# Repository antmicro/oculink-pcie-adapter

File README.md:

# OCuLink to PCIe adapter
Copyright (c) 2025 [Antmicro](https://www.antmicro.com)

## Overview

This project includes PCB design files for an adapter card which break-routes a regular OCuLink x4 connector into x16 PCIe edge card slot.
This board was designed for use with Antmicro [Jetson Orin Baseboard OCuLink Expansion](https://github.com/antmicro/job-oculink-expansion).
Please inspect the schematics and verify the connection diagrams if you plan to use that board with any other OCuLink-compliant accessories.
The PCB design files were prepared in KiCad 9.x 

## Key features

- Supports 4x PCIe link via an OCuLink connector over an x16 card edge connector
- PCIe cards can be powered via USB-C Power Delivery, EPS-12V or Molex Nano-Fit connector
- Optional on-board PCIe clock generator for SRSI and SRNS clocking configurations
- Mechanical outline optimized for  dual slot PCIe cards

## Project structure

The main directory contains KiCad PCB project files and README. 
The remaining files are stored in the following directories:

-   `img` - contains graphics for this README

## Licensing

This project is published under the [Apache-2.0](LICENSE) license.

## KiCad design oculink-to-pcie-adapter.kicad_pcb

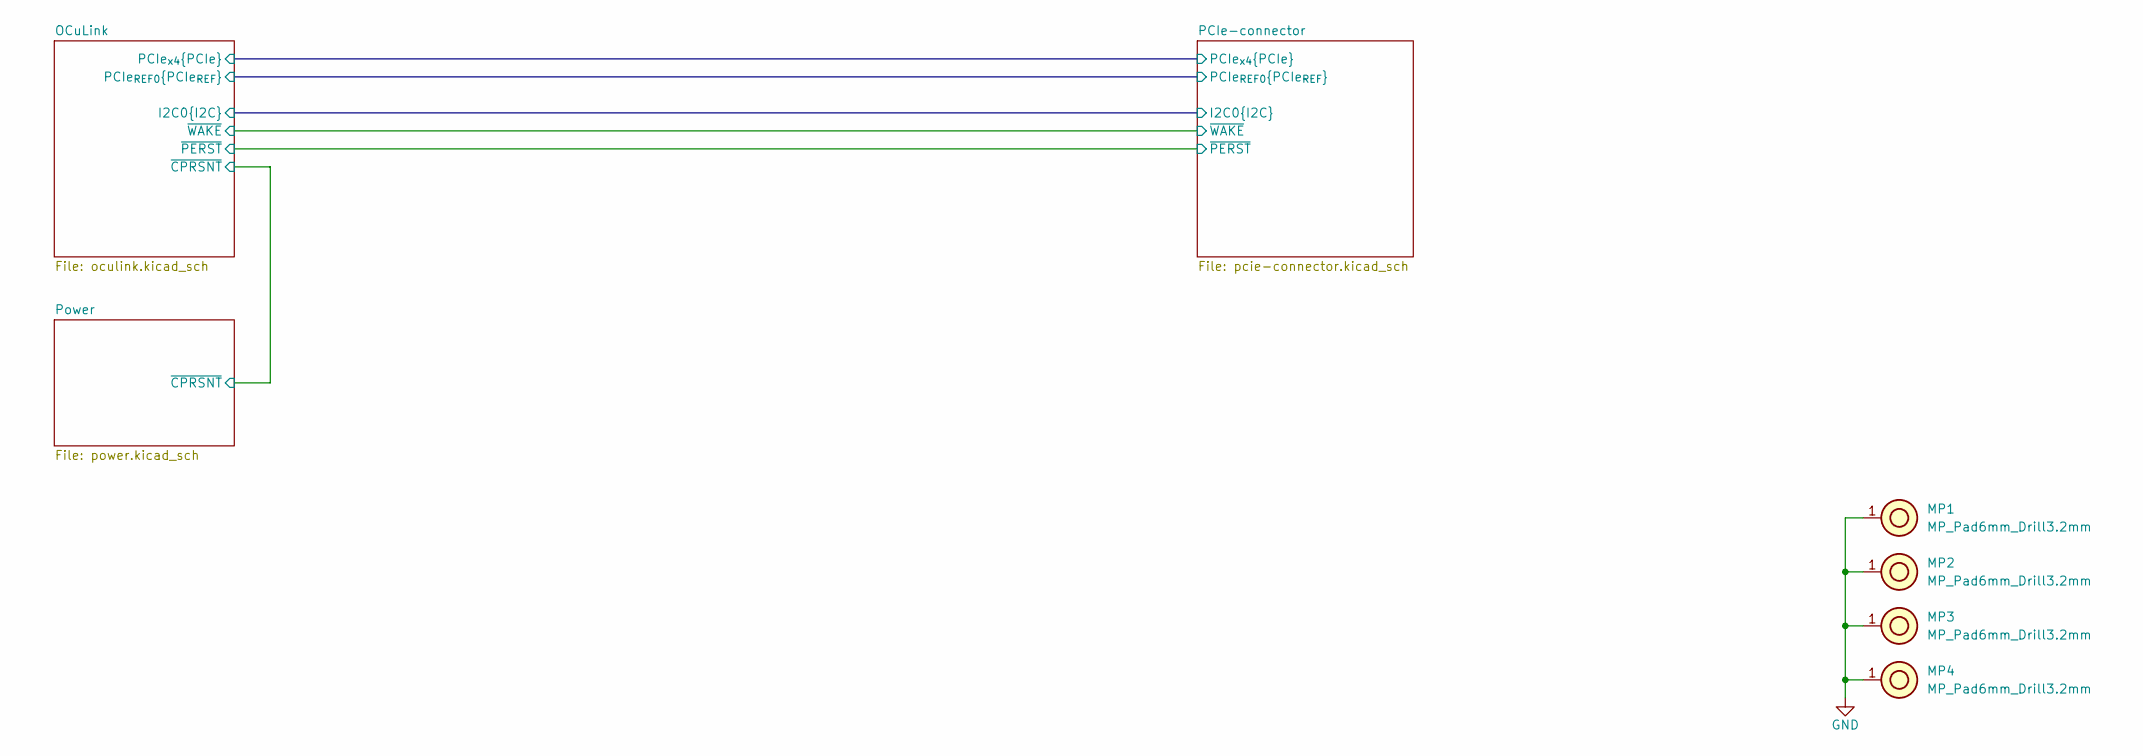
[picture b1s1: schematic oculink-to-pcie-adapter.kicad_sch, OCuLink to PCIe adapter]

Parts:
MP1, MP2, MP3, MP4: MP_Pad6mm_Drill3.2mm

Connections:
GND: MP1.1, MP2.1, MP3.1, MP4.1; also elsewhere on the board

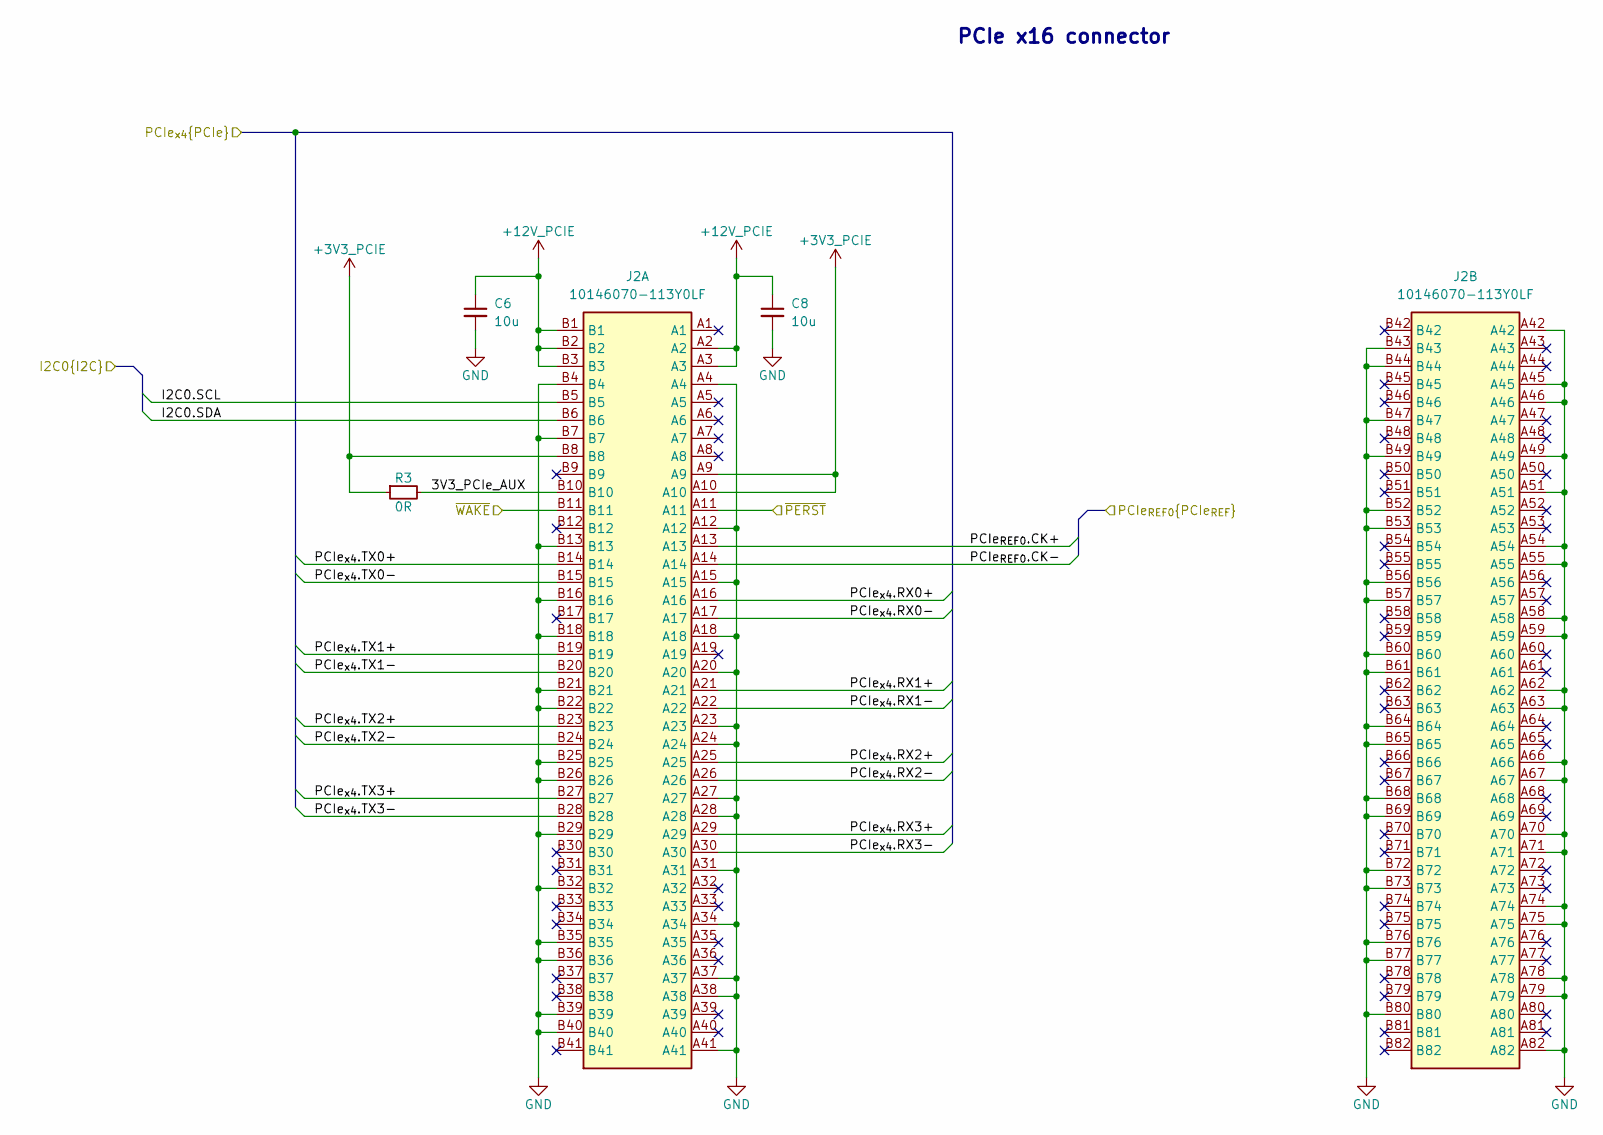
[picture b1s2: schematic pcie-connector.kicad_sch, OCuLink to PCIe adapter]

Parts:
C6, C8: C_10u_0805_35V; C_0805_2012Metric; Voltage 35V; MPN GRM21BR6YA106KE43L
J2: PCIe_x16_10146070-113Y0LF-vertical; AMPHENOL_10146070-113Y0LF; PARTREV E
R3: R_0R_0402; R_0402_1005Metric; MPN ERJ2GE0R00X

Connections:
+3V3_PCIE: J2.A9, J2.A10, J2.B8, R3.1; also elsewhere on the board
+12V_PCIE: C6.1, C8.1, J2.A2, J2.A3, J2.B1, J2.B2, J2.B3; also elsewhere on the board
/OCuLink/I2C0.SCL: J2.B5; also elsewhere on the board
/OCuLink/I2C0.SDA: J2.B6; also elsewhere on the board
/OCuLink/PCIe_{REF0}.CK+: J2.A13; also elsewhere on the board
/OCuLink/PCIe_{REF0}.CK-: J2.A14; also elsewhere on the board
/OCuLink/PCIe_{x4}.RX0+: J2.A16; also elsewhere on the board
/OCuLink/PCIe_{x4}.RX0-: J2.A17; also elsewhere on the board
/OCuLink/PCIe_{x4}.RX1+: J2.A21; also elsewhere on the board
/OCuLink/PCIe_{x4}.RX1-: J2.A22; also elsewhere on the board
/OCuLink/PCIe_{x4}.RX2+: J2.A25; also elsewhere on the board
/OCuLink/PCIe_{x4}.RX2-: J2.A26; also elsewhere on the board
/OCuLink/PCIe_{x4}.RX3+: J2.A29; also elsewhere on the board
/OCuLink/PCIe_{x4}.RX3-: J2.A30; also elsewhere on the board
/OCuLink/PCIe_{x4}.TX0+: J2.B14; also elsewhere on the board
/OCuLink/PCIe_{x4}.TX0-: J2.B15; also elsewhere on the board
/OCuLink/PCIe_{x4}.TX1+: J2.B19; also elsewhere on the board
/OCuLink/PCIe_{x4}.TX1-: J2.B20; also elsewhere on the board
/OCuLink/PCIe_{x4}.TX2+: J2.B23; also elsewhere on the board
/OCuLink/PCIe_{x4}.TX2-: J2.B24; also elsewhere on the board
/OCuLink/PCIe_{x4}.TX3+: J2.B27; also elsewhere on the board
/OCuLink/PCIe_{x4}.TX3-: J2.B28; also elsewhere on the board
/OCuLink/~PERST: J2.A11; also elsewhere on the board
/OCuLink/~WAKE: J2.B11; also elsewhere on the board
/PCIe-connector/3V3_PCIe_AUX: J2.B10, R3.2
GND: C6.2, C8.2, J2.A4, J2.A12, J2.A15, J2.A18, J2.A20, J2.A23, J2.A24, J2.A27, J2.A28, J2.A31, J2.A34, J2.A37, J2.A38, J2.A41, J2.A42, J2.A45, J2.A46, J2.A49, J2.A51, J2.A54, J2.A55, J2.A58, J2.A59, J2.A62, J2.A63, J2.A66, J2.A67, J2.A70, J2.A71, J2.A74, J2.A75, J2.A78, J2.A79, J2.A82, J2.B4, J2.B7, J2.B13, J2.B16, J2.B18, J2.B21, J2.B22, J2.B25, J2.B26, J2.B29, J2.B32, J2.B35, J2.B36, J2.B39, J2.B40, J2.B43, J2.B44, J2.B47, J2.B49, J2.B52, J2.B53, J2.B56, J2.B57, J2.B60, J2.B61, J2.B64, J2.B65, J2.B68, J2.B69, J2.B72, J2.B73, J2.B76, J2.B77, J2.B80; also elsewhere on the board

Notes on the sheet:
PCIe x16 connector

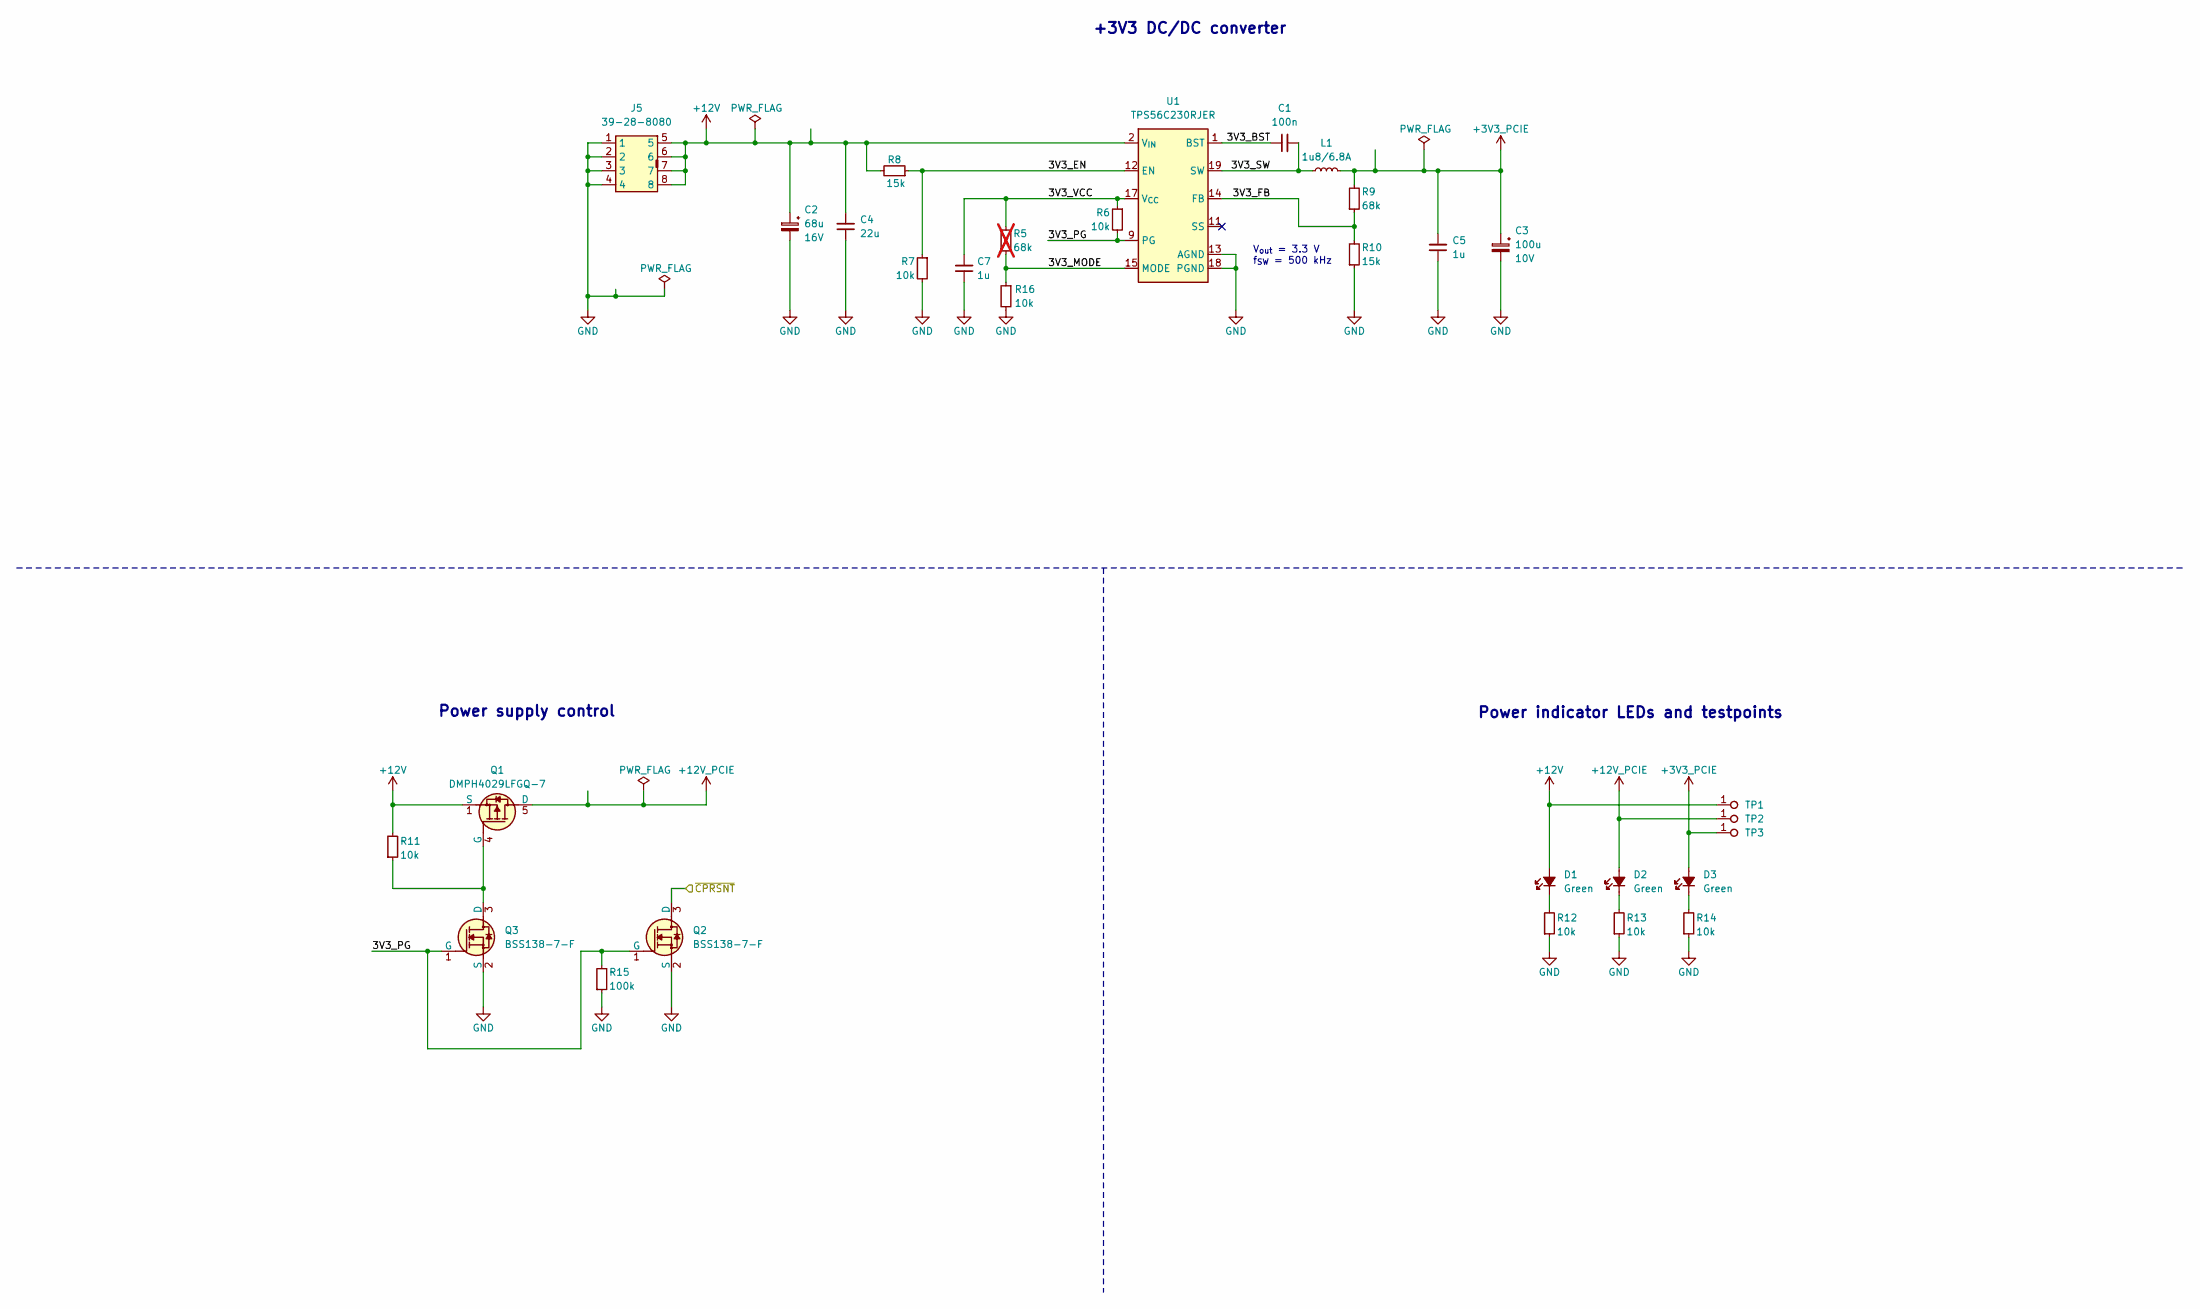
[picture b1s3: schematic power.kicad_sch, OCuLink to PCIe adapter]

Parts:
C1: C_100n_0402; C_0402_1005Metric; Voltage 50V; MPN GRM155R61H104KE14D
C2: C_Pol_68u_16V_Panasonic-TQC-D; C_Pol_EIA-D; Voltage 16V; MPN 16TQC68MYF
C3: C_Pol_100u_10V_KEMET-T520-B; C_Pol_EIA-B; Voltage 10V; MPN T520B107M010ATE070
C4: C_22u_16V_0603; C_0603_1608Metric_EIA; Voltage 16V; MPN CL10A226MO7JZNC
C5, C7: C_1u_0402; C_0402_1005Metric; MPN C1005X6S1A105K050BC
D1, D2, D3: LED_G_0603_LTST-C190GKT; LED_0603_1608Metric_G; MPN LTST-C190GKT
J5: Molex_Mini-Fit-Jr_2x4_39-28-8080; MOLEX_39288080; MPN 39-28-8080
L1: L_1u8_6.8A_WE-MAPI-4020; L_WE-MAPI-4020; MPN 74438356018
Q1: DMPH4029LFGQ; PowerDI3333-8; MPN DMPH4029LFGQ-7
Q2, Q3: BSS138-7-F; SOT-23-3; MPN BSS138-7-F
R5: R_68k_0402; R_0402_1005Metric; Tolerance 1%; MPN CR0402-FX-6802GLF; not fitted
R6, R7, R11, R12, R13, R14, R16: R_10k_0402; R_0402_1005Metric; Tolerance 1%; MPN CR0402-FX-1002GLF
R8, R10: R_15k_0402; R_0402_1005Metric; Tolerance 1%; MPN CR0402-FX-1502GLF
R9: R_68k_0402; R_0402_1005Metric; Tolerance 1%; MPN CR0402-FX-6802GLF
R15: R_100k_0402; R_0402_1005Metric; Tolerance 1%; MPN CR0402-FX-1003GLF
TP1, TP2, TP3: TP_0.75mm_SMD; TP_SMD_0.75mm
U1: TPS56C230; QFN-20-1EP_3x3mm_P0.45mm; MPN TPS56C230RJER

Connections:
+3V3_PCIE: C3.1, C5.2, D3.2 (A), L1.2, R9.2, TP3.1; also elsewhere on the board
+12V: C2.1, C4.2, D1.2 (A), J5.5, J5.6, J5.7, J5.8, Q1.1 (S), Q1.2 (S), Q1.3 (S), R8.2, R11.2, TP1.1, U1.2 (V_{IN}), U1.3 (V_{IN}), U1.4 (V_{IN}), U1.5 (V_{IN})
+12V_PCIE: D2.2 (A), Q1.5 (D), TP2.1; also elsewhere on the board
/OCuLink/~CPRSNT: Q2.3 (D); also elsewhere on the board
/Power/3V3_BST: C1.1, U1.1 (BST)
/Power/3V3_EN: R7.1, R8.1, U1.12 (EN)
/Power/3V3_FB: R9.1, R10.2, U1.14 (FB)
/Power/3V3_MODE: R5.1, R16.1, U1.15 (MODE)
/Power/3V3_PG: Q2.1 (G), Q3.1 (G), R6.2, R15.2, U1.9 (PG)
/Power/3V3_SW: C1.2, L1.1, U1.6 (SW), U1.19 (SW), U1.20 (SW)
/Power/3V3_VCC: C7.2, R5.2, R6.1, U1.17 (V_{CC})
GND: C2.2, C3.2, C4.1, C5.1, C7.1, J5.1, J5.2, J5.3, J5.4, Q2.2 (S), Q3.2 (S), R7.2, R10.1, R12.1, R13.1, R14.1, R15.1, R16.2, U1.7 (PGND), U1.8 (PGND), U1.13 (AGND), U1.18 (PGND), U1.21 (PGND); also elsewhere on the board
unnamed: D1.1 (C), R12.2
unnamed: D2.1 (C), R13.2
unnamed: D3.1 (C), R14.2
unnamed: Q1.4 (G), Q3.3 (D), R11.1

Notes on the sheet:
V_{out} = 3.3 V f_{SW} = 500 kHz
+3V3 DC/DC converter
Power indicator LEDs and testpoints
Power supply control

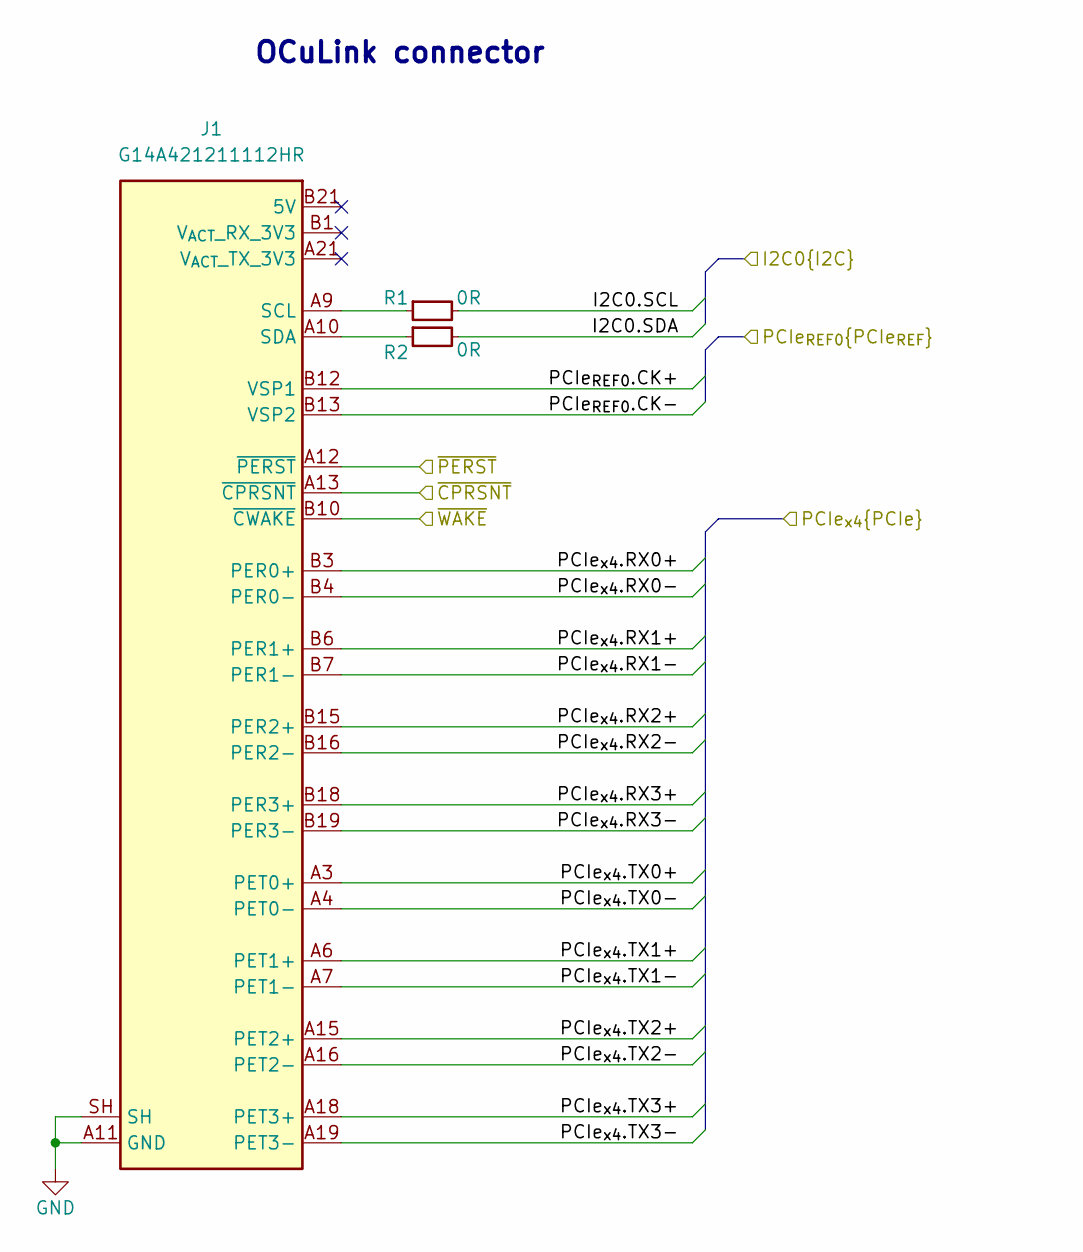
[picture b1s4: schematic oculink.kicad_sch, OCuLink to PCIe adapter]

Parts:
J1: OCuLink_x4_Amphenol_G14A421211112HR; Amphenol_G14A421211112HR; MPN G14A421211112HR
R1, R2: R_0R_0402; R_0402_1005Metric; MPN ERJ2GE0R00X

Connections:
/OCuLink/I2C0.SCL: R1.2; also elsewhere on the board
/OCuLink/I2C0.SDA: R2.2; also elsewhere on the board
/OCuLink/PCIe_{REF0}.CK+: J1.B12 (VSP1); also elsewhere on the board
/OCuLink/PCIe_{REF0}.CK-: J1.B13 (VSP2); also elsewhere on the board
/OCuLink/PCIe_{x4}.RX0+: J1.B3 (PER0+); also elsewhere on the board
/OCuLink/PCIe_{x4}.RX0-: J1.B4 (PER0-); also elsewhere on the board
/OCuLink/PCIe_{x4}.RX1+: J1.B6 (PER1+); also elsewhere on the board
/OCuLink/PCIe_{x4}.RX1-: J1.B7 (PER1-); also elsewhere on the board
/OCuLink/PCIe_{x4}.RX2+: J1.B15 (PER2+); also elsewhere on the board
/OCuLink/PCIe_{x4}.RX2-: J1.B16 (PER2-); also elsewhere on the board
/OCuLink/PCIe_{x4}.RX3+: J1.B18 (PER3+); also elsewhere on the board
/OCuLink/PCIe_{x4}.RX3-: J1.B19 (PER3-); also elsewhere on the board
/OCuLink/PCIe_{x4}.TX0+: J1.A3 (PET0+); also elsewhere on the board
/OCuLink/PCIe_{x4}.TX0-: J1.A4 (PET0-); also elsewhere on the board
/OCuLink/PCIe_{x4}.TX1+: J1.A6 (PET1+); also elsewhere on the board
/OCuLink/PCIe_{x4}.TX1-: J1.A7 (PET1-); also elsewhere on the board
/OCuLink/PCIe_{x4}.TX2+: J1.A15 (PET2+); also elsewhere on the board
/OCuLink/PCIe_{x4}.TX2-: J1.A16 (PET2-); also elsewhere on the board
/OCuLink/PCIe_{x4}.TX3+: J1.A18 (PET3+); also elsewhere on the board
/OCuLink/PCIe_{x4}.TX3-: J1.A19 (PET3-); also elsewhere on the board
/OCuLink/~CPRSNT: J1.A13 (~CPRSNT); also elsewhere on the board
/OCuLink/~PERST: J1.A12 (~PERST); also elsewhere on the board
/OCuLink/~WAKE: J1.B10 (~CWAKE); also elsewhere on the board
GND: J1.A2 (GND), J1.A5 (GND), J1.A8 (GND), J1.A11 (GND), J1.A14 (GND), J1.A17 (GND), J1.A20 (GND), J1.B2 (GND), J1.B5 (GND), J1.B8 (GND), J1.B11 (GND), J1.B14 (GND), J1.B17 (GND), J1.B20 (GND), J1.SH; also elsewhere on the board
unnamed: J1.A9 (SCL), R1.1
unnamed: J1.A10 (SDA), R2.1

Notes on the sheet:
OCuLink connector

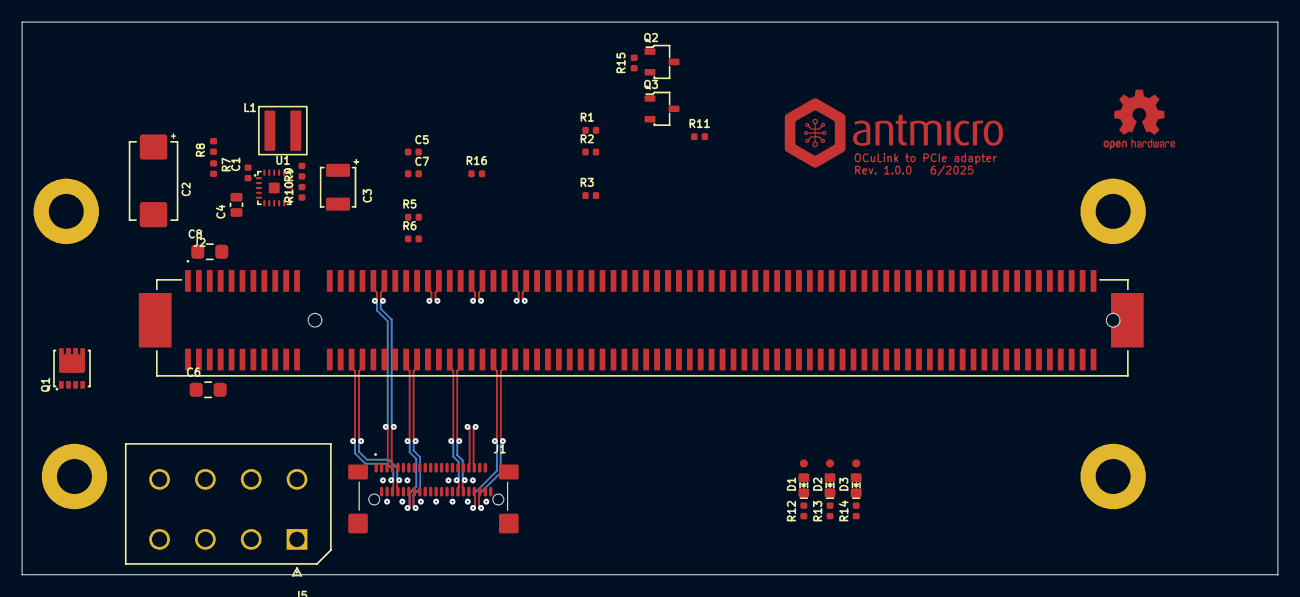
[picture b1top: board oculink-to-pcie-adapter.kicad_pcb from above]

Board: 4 copper layers, 115.1 x 50.6 mm, 41 parts (0 on the bottom side), 41 nets.

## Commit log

2025-06-18 Add README
2025-06-18 [#79026] Add gitignore, init project
2025-06-18 [#79026] Add OCuLink and PCIex16 connectors, connect them together
2025-06-18 [#79026] Add power supply section, reannotate schematic
2025-06-20 [#79026] Change power input connector, add net classes, minor schematic refactor
2025-06-20 [#79262] Begin component placement, add 12V PCIe decoupling capacitors, reduce inductor size
2025-06-20 [#79262] Define stackup and PCIe differential pair parameters, start layout
2025-06-20 [#79262] Add USB PD input, 12V DC-DC converter, power ORing
2025-06-20 [#79262] Move ideal diodes and Molex connector to separate schematic sheet
2025-06-24 [#79262] Change TVS diodes, adjust LEDs resistors, refactor USB-PD schematic
2025-06-24 [#79262] Cleanup 12V DC-DC converter, move Molex connector to root sheet
2025-06-24 [#79262] Finish power section schematic
2025-06-24 [#79262] Add TVS to OCuLink connector, add decoupling capacitors for PCIe connector
2025-06-24 [#79262] BOM consolidation
2025-06-24 [#79262] Add TVS to 12V power pins
2025-06-24 [#79262] Further BOM consolidation
2025-06-24 [#79262] WIP: Begin component placement
2025-06-25 [#79262] Remove 12V DC-DC R_boot resistor
2025-06-25 [#79262] Reduce Q4 max Vgs
2025-06-25 [#79262] Perform component placement of 12V DC-DC converter, USB PD section and ideal diodes
2025-06-25 [#79262] Fix directions of hierarchical labels
2025-06-25 [#79262] Change USB PD controller to CYPD3177
2025-06-27 [#79426] Add optional clock generator
2025-06-27 [#79426] Add 0R to OCuLink control signals
2025-06-27 [#79426] Connect DC input connectors via ideal diodes, change 15V TVS to 12V TVS
2025-06-27 [#79426] Fix USB-PD fault LED to prevent excessive MOSFET Vgs
2025-06-27 [#79426] Add PCIe power connector
2025-06-27 [#79426] Change Q3 MOSFET
2025-06-27 [#79426] Change 3V3 DC-DC UVLO to 11.3V
2025-06-27 [#79426] Minor USB-C PD schematic fixes
2025-06-27 [#79426] Small USB-PD improvements
2025-06-27 [#79426] Removed power sequencing, added PERST control
2025-06-27 [#79262] WIP: Component placement
2025-06-30 Added .ci.yml
2025-06-30 [#79262] Adjusted placement
2025-06-30 [#79262] Added User.9 layer
2025-06-30 [#79262] Rotated the board files
2025-07-01 [#79262] Route high speed and power
2025-07-02 [#79262] Connect all the signals
2025-07-02 [#79262] Place silkscreen
2025-07-02 [#79262] Clean up tracks and vias
2025-07-02 [#79262] DRC clean
2025-07-02 [#79262] Fix PCIe deskew
2025-07-02 [#79262] Add PCB SHA
2025-07-02 Added README.md
2025-07-07 [#79790] Made board smaller, moved connectors to shorter edge
2025-07-08 [#79790] Finalized rerouting
2025-07-08 [#79790] Slight silkscreen improvements
2025-07-08 [#79790] Reduced board size to integer amount of mm
2025-07-08 Updated render image and schematic pdf
2025-07-09 [#79790] Added fiducials and double sided test points
2025-07-09 Update schematic pdf and README image
2025-07-11 [#79790] Applied review fixes
2025-07-11 [#79790] Fixed pinout of OCuLink
2025-07-16 Add OHP badge and licensing info
2025-07-16 Update render naming

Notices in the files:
parts and their libraries:
License: Apache-2.0
